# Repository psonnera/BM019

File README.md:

# BM019
Eagle version of OSHW BM019
Find original data at http://www.solutions-cubed.com/bm019/
Nice free Gerber viewer at https://www.zofzpcb.com/

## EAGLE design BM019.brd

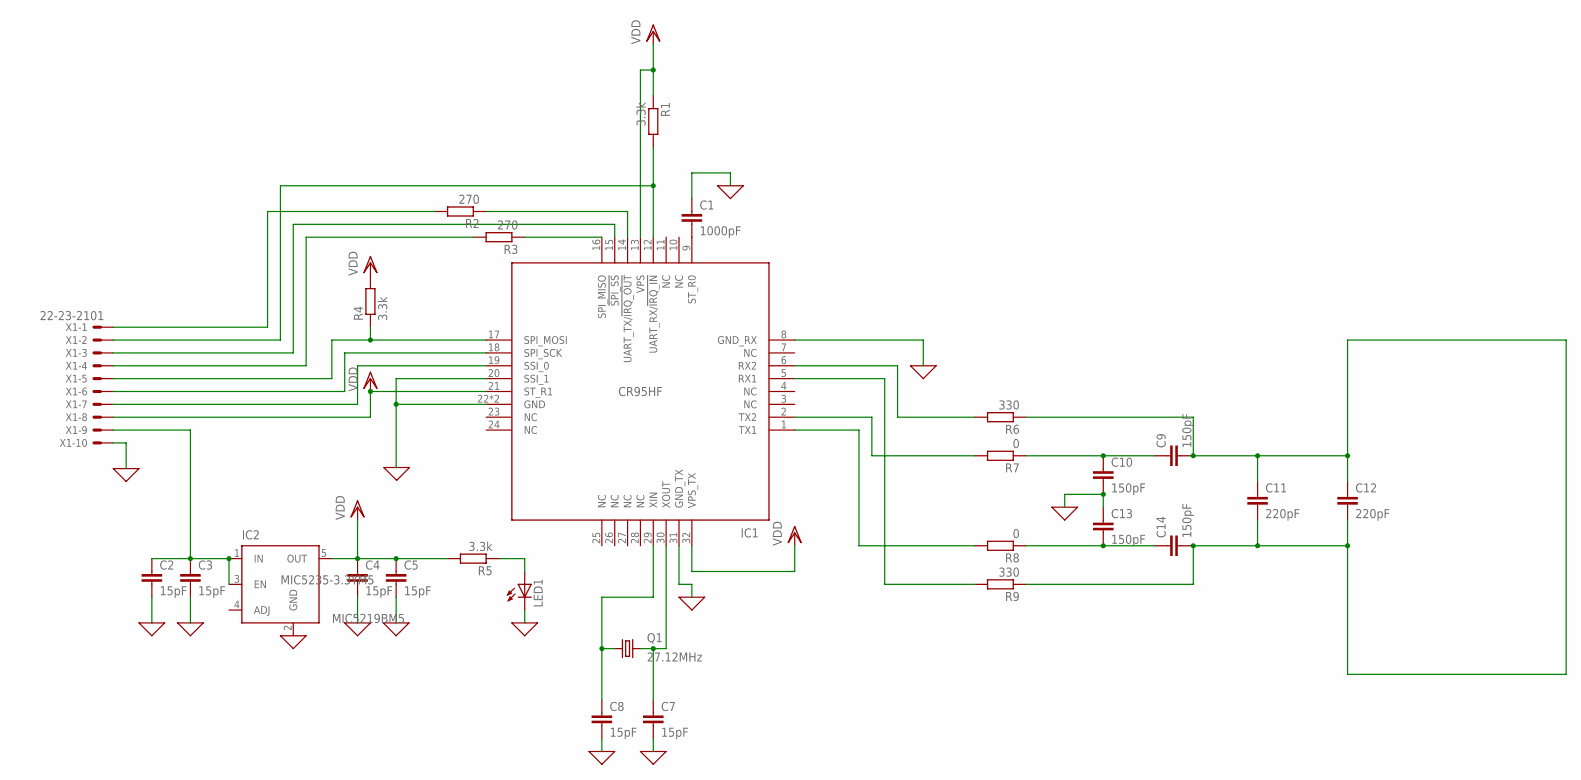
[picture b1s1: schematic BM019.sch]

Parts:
C1: 1000pF; C0603
C2, C3, C4, C5, C7, C8: 15pF; C0603
C9, C10, C13, C14: 150pF; C0603
C11, C12: 220pF; C0603
IC1: CR95HF; QFN32(5X5)
IC2: MIC5219BM5; SOT23-5; MPN MIC5235-3.3YM5
LED1: LEDCHIP-LED0603; CHIP-LED0603
Q1: 27.12MHz; 2.0X1.6_KX-5
R1, R4, R5: 3.3k; R0603
R2, R3: 270; R0603
R6, R9: 330; R0603
R7, R8: 0; R0805
X1: 22-23-2101

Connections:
0: C1.1, C2.2, C3.2, C4.2, C5.2, C7.2, C8.2, C10.2, C13.1, IC1.8 (GND_RX), IC1.20 (SSI_1), IC1.22 (GND), IC1.31 (GND_TX), IC1.33 (GND), LED1.C, X1.10
GND: IC2.2 (GND)
unnamed: C1.2, IC1.9 (ST_R0)
unnamed: LED1.A, R5.1
unnamed: IC1.19 (SSI_0), X1.7
unnamed: C2.1, C3.1, IC2.1 (IN), IC2.3 (EN), X1.9
unnamed: IC1.6 (RX2), R6.2
unnamed: IC1.16 (SPI_MISO), R3.1
unnamed: IC1.14 (UART_TX/!IRQ_OUT), R2.1
unnamed: IC1.17 (SPI_MOSI), R4.1, X1.5
unnamed: IC1.18 (SPI_SCK), X1.6
unnamed: R3.2, X1.4
unnamed: IC1.12 (UART_RX/!IRQ_IN), R1.2, X1.2
unnamed: C8.1, IC1.29 (XIN), Q1.1
unnamed: C7.1, IC1.30 (XOUT), Q1.3 (2)
unnamed: R2.2, X1.1
unnamed: IC1.5 (RX1), R9.2
unnamed: IC1.15 (!SPI_SS), X1.3
unnamed: C9.2, C11.1, C11.2, C12.1, C12.2, C14.2, R6.1, R9.1
unnamed: C9.1, C10.1, R7.1
unnamed: C13.2, C14.1, R8.1
unnamed: IC1.2 (TX2), R7.2
unnamed: IC1.1 (TX1), R8.2
VDD: C4.1, C5.1, IC1.13 (VPS), IC1.21 (ST_R1), IC1.32 (VPS_TX), IC2.5 (OUT), R1.1, R4.2, R5.2, X1.8

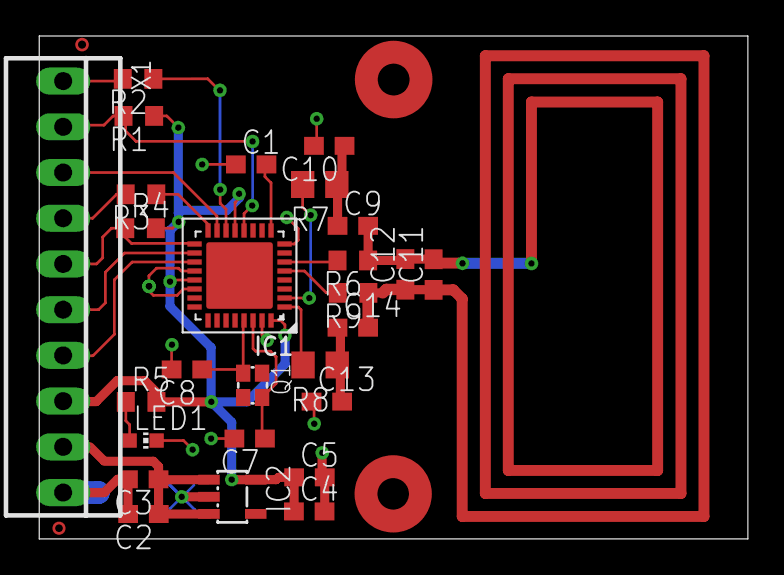
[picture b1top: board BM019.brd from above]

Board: 2 copper layers, 39.4 x 27.9 mm, 27 parts (0 on the bottom side), 23 nets.

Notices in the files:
parts and their libraries:
crystal-geyer_V1_0: Copyright: Geyer-Electronic
